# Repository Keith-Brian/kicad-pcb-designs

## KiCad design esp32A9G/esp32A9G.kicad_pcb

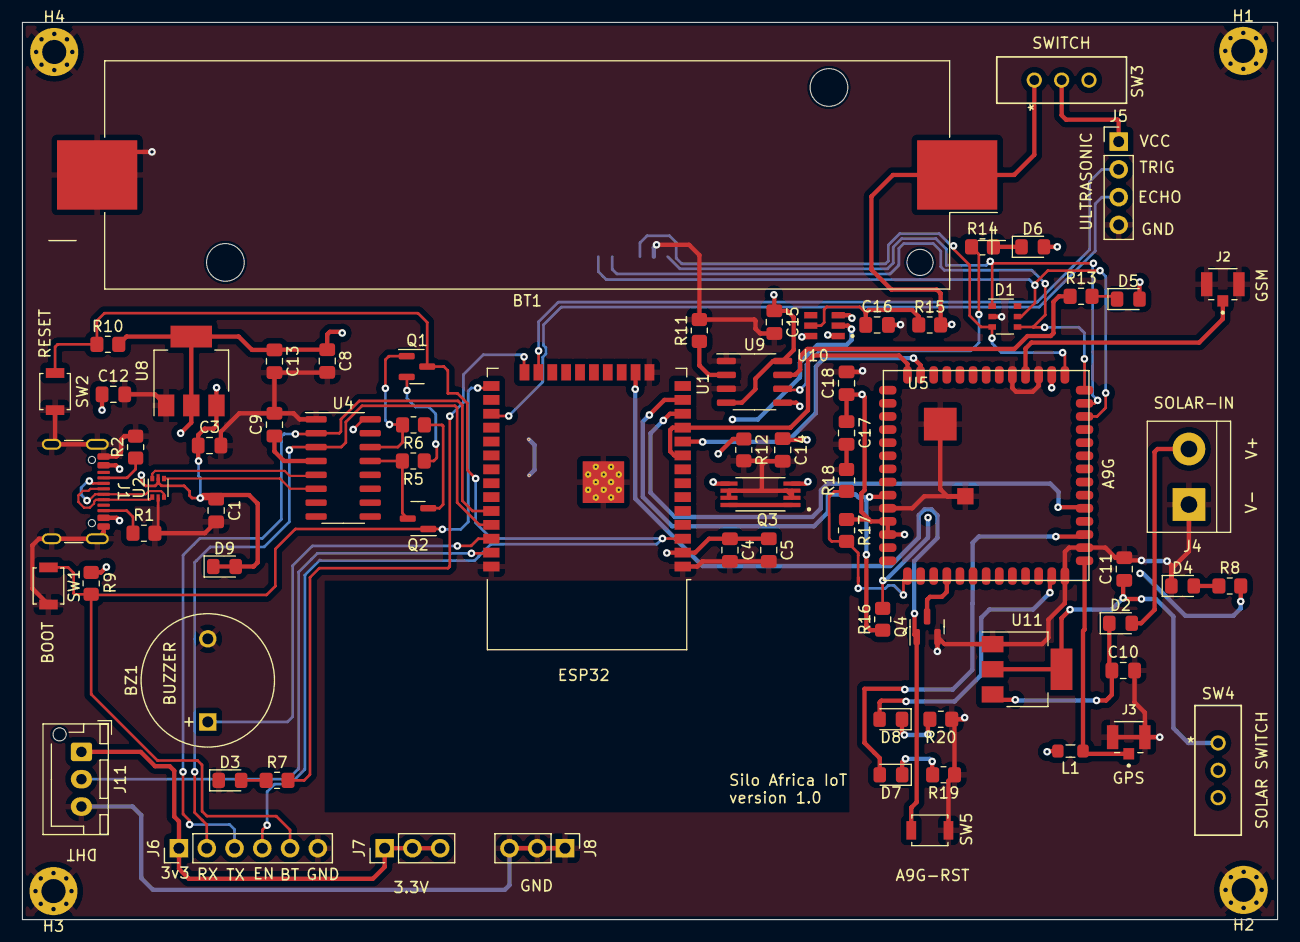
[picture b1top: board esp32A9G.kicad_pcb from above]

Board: 4 copper layers, 114.8 x 82.1 mm, 76 parts (1 on the bottom side), 57 nets.

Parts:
BT1: Battery; BatteryHolder_Keystone_1042_1x18650
BZ1: Buzzer; MagneticBuzzer_ProSignal_ABI-009-RC
C1, C4, C11, C12: 22uF; C_0805_2012Metric_Pad1.18x1.45mm_HandSolder
C3, C5, C8, C9: 0.1uF; C_0805_2012Metric_Pad1.18x1.45mm_HandSolder
C10, C13, C14, C15, C16, C17: 10uF; C_0805_2012Metric_Pad1.18x1.45mm_HandSolder
C18: 100uF; C_0805_2012Metric_Pad1.18x1.45mm_HandSolder
D1: SMF05C; TSOP-6_1.65x3.05mm_P0.95mm
D2: 1N4001; D_0805_2012Metric_Pad1.15x1.40mm_HandSolder
D3, D4, D5, D6, D7, D8: LED; LED_0805_2012Metric_Pad1.15x1.40mm_HandSolder
D9: D_Schottky; D_0805_2012Metric_Pad1.15x1.40mm_HandSolder
H1, H2, H3, H4: MountingHole_Pad; MountingHole_2.2mm_M2_Pad_Via
J1: USB_C_Receptacle_USB2.0; USB_C_Receptacle_GCT_USB4105-xx-A_16P_TopMnt_Horizontal
J2, J3: CONUFL001-SMD-T; LINX_CONUFL001-SMD-T
J4: Screw_Terminal_01x02; TerminalBlock_bornier-2_P5.08mm
J5: Conn_01x04_Pin; PinHeader_1x04_P2.54mm_Vertical
J6: Conn_01x06_Pin; PinHeader_1x06_P2.54mm_Vertical
J7, J8: Conn_01x03_Pin; PinHeader_1x03_P2.54mm_Vertical
J9: MICRO SIM; GCT_SIM7100-6-1-15-00-A_REVC
J11: Conn_01x03_Pin; JST_XH_B3B-XH-AM_1x03_P2.50mm_Vertical
L1: L; L_0805_2012Metric_Pad1.05x1.20mm_HandSolder
Q1: 2N3904; SOT-23
Q2: 2N3906; SOT-23
Q3: FS8205A; SOP65P640X120-8N
Q4: 2N7002; SOT-23
R1, R2: 5k1; R_0805_2012Metric_Pad1.20x1.40mm_HandSolder
R5, R9, R10, R16: 10k; R_0805_2012Metric_Pad1.20x1.40mm_HandSolder
R6: 10K; R_0805_2012Metric_Pad1.20x1.40mm_HandSolder
R7, R17, R18: 330E; R_0805_2012Metric_Pad1.20x1.40mm_HandSolder
R8, R12, R13, R14, R19, R20: 1k; R_0805_2012Metric_Pad1.20x1.40mm_HandSolder
R11: 1k6; R_0805_2012Metric_Pad1.20x1.40mm_HandSolder
R15: 100; R_0805_2012Metric_Pad1.20x1.40mm_HandSolder
SW1, SW2, SW5: SW_Push; SW_SPST_B3U-1000P
SW3: SW_SPST; slider
SW4: SW_SPDT; slider
U1: ESP32-WROOM-32D
U2: USBLC6-2P6; SOT-666
U4: CH340C; SOIC-16_3.9x9.9mm_P1.27mm
U5: A9G; A9
U8: LM1117MP-3.3; SOT-223-3_TabPin2
U9: TP4056; SO-8_3.9x4.9mm_P1.27mm
U10: DW01A; SOT95P280X145-6N
U11: AMS1117-5.0; SOT-223-3_TabPin2

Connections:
+3V3: C4.1, C5.1, C8.1, C13.1, J6.1, J7.1, J7.2, J7.3, J11.1, R8.2, R9.2, R10.2, U1.2 (VDD), U4.16 (VCC), U8.2 (VO)
/A9G_RST: Q4.1 (G), SW5.1, U1.16 (IO13)
/ADC_0: R17.2, R18.1, U5.15 (ADC0)
/BOOT: J6.5, Q2.1 (E), R9.1, SW1.1, U1.25 (IO0)
/BUZZER: BZ1.1 (-), U1.36 (IO22)
/D+: U2.6 (I/O1), U4.5 (UD+)
/D-: U2.4 (I/O2), U4.6 (UD-)
/DE+: J1.A6 (D+), J1.B6 (D+), U2.1 (I/O1)
/DE-: J1.A7 (D-), J1.B7 (D-), U2.3 (I/O2)
/DHT11: J11.2, U1.37 (IO23)
/DTR: Q2.3 (C), R5.2, U4.13 (~DTR)
/ECHO: J5.3, U1.27 (IO16)
/EN: J6.4, Q1.3 (C), R10.1, SW2.1, U1.3 (EN)
/GPRS_LED: D8.2 (A), U5.26 (IO27)
/GSM_LED: D7.2 (A), U5.30 (IO28)
/LED: R7.2, U1.24 (IO2)
/LOW_PWR: U1.12 (IO27), U5.32 (IO25)
/OC: Q3.4, U10.3 (OC)
/OD: Q3.5, U10.1 (OD)
/PWR_KEY: R16.1, U1.13 (IO14), U5.9 (PWRKEY)
/RTS: Q1.1 (E), R6.2, U4.14 (~RTS)
/RX: J6.2, U1.35 (TXD0/IO1), U4.3 (RXD)
/SIM_CLK: D1.4, J9.C3 (CLK), U5.41 (SIM_CLK)
/SIM_DATA: D1.5, J9.C7 (I/O), U5.39 (SIM_DIO)
/SIM_RST: D1.3, J9.C2 (RST), U5.42 (SIM_RST)
/SIM_VDD: D1.1, J9.C1 (VCC), U5.40 (VSIM)
/TRIG: J5.2, U1.23 (IO15)
/TX: J6.3, U1.34 (RXD0/IO3), U4.2 (TXD)
/UART_RX: U1.10 (IO25), U5.53 (UART1_RX)
/UART_TX: U1.9 (IO33), U1.11 (IO26), U5.54 (UART1_TX)
/V3: C9.1, U4.4 (V3)
/VIO: R16.2, U5.43 (V_IO)
BATT_IN: BT1.1 (+), C14.1, R15.2, SW3.1 (A), U9.5 (BAT)
GND: BT1.2 (-), BZ1.2 (+), C1.2, C3.2, C4.2, C5.2, C8.2, C9.2, C10.2, C11.2, C12.2, C13.2, C14.2, C15.2, C16.2, C17.2, C18.2, D1.2, D3.1 (K), D4.1 (K), H1.1, H2.1, H3.1, H4.1, J1.A1 (GND), J1.A12 (GND), J1.B1 (GND), J1.B12 (GND), J1.S1 (SHIELD), J2.2, J2.3, J3.2, J3.3, J4.1, J5.4, J6.6, J8.1, J8.2, J8.3, J9.C5 (GND), J11.3, Q3.2, Q3.3, Q3.6, Q3.7, Q4.2 (S), R1.2, R2.2, R11.2, R12.2, R18.2, R19.1, R20.1, SW1.2, SW2.2, SW5.2, U1.1 (GND), U1.15 (GND), U1.38 (GND), U1.39 (GND), U2.2 (GND), U4.1 (GND), U5.10 (GND), U5.27 (GND_1), U5.29 (GND_2), U5.44 (GND_3), U5.46 (GND_4), U5.55 (GND_5), U5.56 (GND_6), U8.1 (GND), U9.1 (TEMP), U9.3 (GND), U10.6 (GND), U11.1 (GND)
GPRS_RF: J2.1, U5.45 (GPRS_RF)
GPS_RF: J3.1, L1.1, U5.28 (GPS_RF)
unnamed: D2.2 (A), J4.2
unnamed: C10.1, D2.1 (K), U11.3 (VI)
unnamed: D3.2 (A), R7.1
unnamed: D4.2 (A), R8.1
unnamed: D5.1 (K), R13.2
unnamed: D6.1 (K), R14.2
unnamed: D7.1 (K), R19.2
unnamed: D8.1 (K), R20.2
unnamed: J1.A5 (CC1), R2.1
unnamed: J1.B5 (CC2), R1.1
unnamed: Q1.2 (B), R5.1
unnamed: Q2.2 (B), R6.1
unnamed: Q4.3 (D), U5.18 (RESET)
unnamed: R11.1, U9.2 (PROG)
unnamed: R13.1, U9.7 (~CHRG)
unnamed: R14.1, U9.6 (~STDBY)
unnamed: R12.1, U10.2 (CS)
unnamed: C16.1, R15.1, U10.5 (VCC)
SOLAR_IN: C11.1, SW4.1 (A), U11.2 (VO)
VBAT: C1.1, C3.1, C12.1, C17.1, C18.1, D9.1 (K), D9.2 (A), J1.A4 (VBUS), J1.A9 (VBUS), J1.B4 (VBUS), J1.B9 (VBUS), J5.1, L1.2, R17.1, SW3.2 (B), SW4.3 (C), U2.5 (VBUS), U5.11 (VBAT), U5.12 (VBATT), U8.3 (VI)
VCC: C15.1, D5.2 (A), D6.2 (A), SW4.2 (B), U9.4 (VCC), U9.8 (CE)

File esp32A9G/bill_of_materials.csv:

"Id";"Designator";"Footprint";"Quantity";"Designation";"Supplier and ref";
1;"C12,C11,C4,C1";"C_0805_2012Metric_Pad1.18x1.45mm_HandSolder";4;"22uF";;;
2;"D4,D3,D8,D7,D5,D6";"LED_0805_2012Metric_Pad1.15x1.40mm_HandSolder";6;"LED";;;
3;"C18";"C_0805_2012Metric_Pad1.18x1.45mm_HandSolder";1;"100uF";;;
4;"BT1";"BatteryHolder_Keystone_1042_1x18650";1;"Battery";;;
5;"C14,C17,C15,C16,C13,C10";"C_0805_2012Metric_Pad1.18x1.45mm_HandSolder";6;"10uF";;;
6;"R7,R18,R17";"R_0805_2012Metric_Pad1.20x1.40mm_HandSolder";3;"330E";;;
7;"D2";"D_0805_2012Metric_Pad1.15x1.40mm_HandSolder";1;"1N4001";;;
8;"SW3";"slider";1;"SW_SPST";;;
9;"SW5,SW2,SW1";"SW_SPST_B3U-1000P";3;"SW_Push";;;
10;"U4";"SOIC-16_3.9x9.9mm_P1.27mm";1;"CH340C";;;
11;"R12,R14,R20,R13,R8,R19";"R_0805_2012Metric_Pad1.20x1.40mm_HandSolder";6;"1k";;;
12;"H1,H2,H3,H4";"MountingHole_2.2mm_M2_Pad_Via";4;"MountingHole_Pad";;;
13;"L1";"L_0805_2012Metric_Pad1.05x1.20mm_HandSolder";1;"L";;;
14;"R11";"R_0805_2012Metric_Pad1.20x1.40mm_HandSolder";1;"1k6";;;
15;"J11";"JST_XH_B3B-XH-AM_1x03_P2.50mm_Vertical";1;"Conn_01x03_Pin";;;
16;"Q2";"SOT-23";1;"2N3906";;;
17;"C9,C5,C8,C3";"C_0805_2012Metric_Pad1.18x1.45mm_HandSolder";4;"0.1uF";;;
18;"R6";"R_0805_2012Metric_Pad1.20x1.40mm_HandSolder";1;"10K";;;
19;"J5";"PinHeader_1x04_P2.54mm_Vertical";1;"Conn_01x04_Pin";;;
20;"U11";"SOT-223-3_TabPin2";1;"AMS1117-5.0";;;
21;"R15";"R_0805_2012Metric_Pad1.20x1.40mm_HandSolder";1;"100";;;
22;"R10,R5,R16,R9";"R_0805_2012Metric_Pad1.20x1.40mm_HandSolder";4;"10k";;;
23;"J1";"USB_C_Receptacle_GCT_USB4105-xx-A_16P_TopMnt_Horizontal";1;"USB_C_Receptacle_USB2.0";;;
24;"Q3";"SOP65P640X120-8N";1;"FS8205A";;;
25;"BZ1";"MagneticBuzzer_ProSignal_ABI-009-RC";1;"Buzzer";;;
26;"Q4";"SOT-23";1;"2N7002";;;
27;"J7,J8";"PinHeader_1x03_P2.54mm_Vertical";2;"Conn_01x03_Pin";;;
28;"D9";"D_0805_2012Metric_Pad1.15x1.40mm_HandSolder";1;"D_Schottky";;;
29;"Q1";"SOT-23";1;"2N3904";;;
30;"J3,J2";"LINX_CONUFL001-SMD-T";2;"CONUFL001-SMD-T";;;
31;"U5";"A9";1;"A9G";;;
32;"J4";"TerminalBlock_bornier-2_P5.08mm";1;"Screw_Terminal_01x02";;;
33;"D1";"TSOP-6_1.65x3.05mm_P0.95mm";1;"SMF05C";;;
34;"SW4";"slider";1;"SW_SPDT";;;
35;"U1";"ESP32-WROOM-32D";1;"ESP32-WROOM-32D";;;
36;"U8";"SOT-223-3_TabPin2";1;"LM1117MP-3.3";;;
37;"R1,R2";"R_0805_2012Metric_Pad1.20x1.40mm_HandSolder";2;"5k1";;;
38;"U2";"SOT-666";1;"USBLC6-2P6";;;
39;"J6";"PinHeader_1x06_P2.54mm_Vertical";1;"Conn_01x06_Pin";;;
40;"U10";"SOT95P280X145-6N";1;"DW01A";;;
41;"U9";"SO-8_3.9x4.9mm_P1.27mm";1;"TP4056";;;
42;"J9";"GCT_SIM7100-6-1-15-00-A_REVC";1;"MICRO SIM";;;

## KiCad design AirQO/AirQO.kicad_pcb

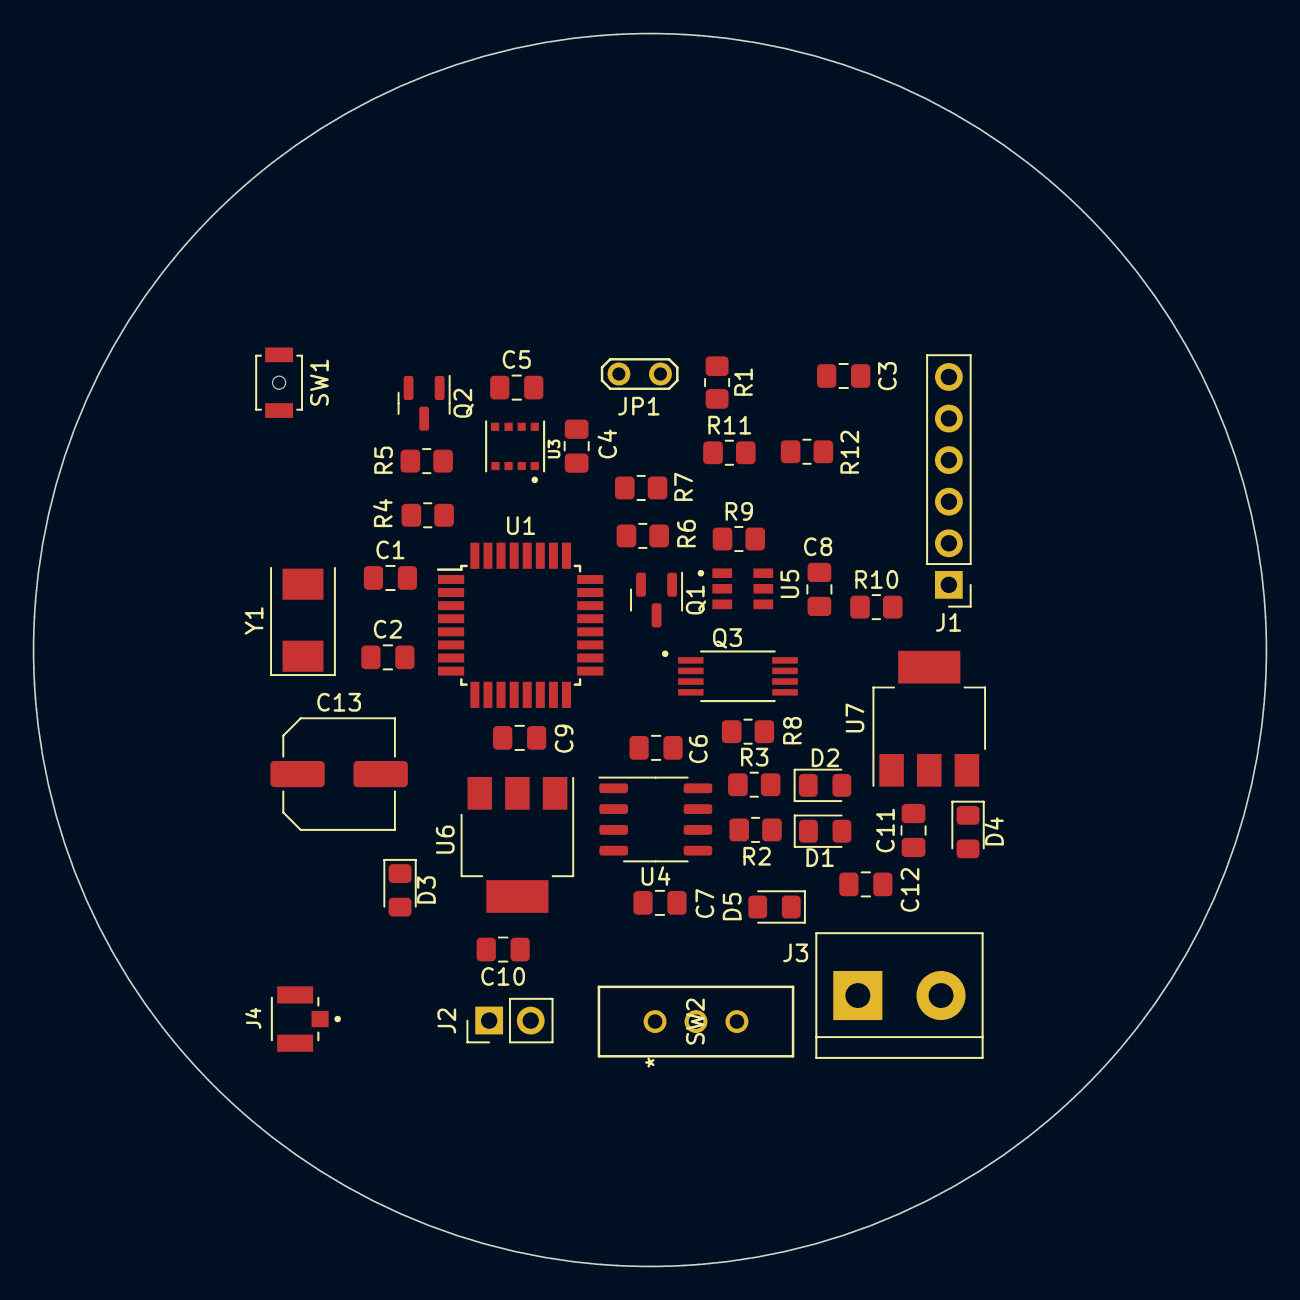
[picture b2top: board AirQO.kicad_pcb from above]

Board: 2 copper layers, 75.3 x 75.3 mm, 48 parts (1 on the bottom side), 35 nets, no tracks yet.

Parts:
C1, C2: 22pF; C_0805_2012Metric_Pad1.18x1.45mm_HandSolder
C3: 100nF; C_0805_2012Metric_Pad1.18x1.45mm_HandSolder
C4, C5: 0.1uF; C_0805_2012Metric_Pad1.18x1.45mm_HandSolder
C6, C7, C8, C10, C11: 10uF; C_0805_2012Metric_Pad1.18x1.45mm_HandSolder
C9, C12: 22uF; C_0805_2012Metric_Pad1.18x1.45mm_HandSolder
C13: 22pF; C_Elec_6.3x7.7
D1, D2: LED; LED_0805_2012Metric_Pad1.15x1.40mm_HandSolder
D3, D4, D5: 1N4001; D_0805_2012Metric_Pad1.15x1.40mm_HandSolder
J1: Conn_01x06_Pin; PinHeader_1x06_P2.54mm_Vertical
J2: Conn_01x02_Pin; PinHeader_1x02_P2.54mm_Vertical
J3: Screw_Terminal_01x02; TerminalBlock_bornier-2_P5.08mm
J4: CONUFL001-SMD-T; LINX_CONUFL001-SMD-T
JP1: Jumper_2_Open; TestPoint_2Pads_Pitch2.54mm_Drill0.8mm
Q1, Q2: 2N7002; SOT-23
Q3: FS8205A; SOP65P640X120-8N
R1, R4, R5, R6, R7: 10k; R_0805_2012Metric_Pad1.20x1.40mm_HandSolder
R2, R3, R9, R11, R12: 1k; R_0805_2012Metric_Pad1.20x1.40mm_HandSolder
R8: 1k6; R_0805_2012Metric_Pad1.20x1.40mm_HandSolder
R10: 100; R_0805_2012Metric_Pad1.20x1.40mm_HandSolder
SW1: SW_Push; SW_SPST_B3U-1000P-B
SW2: SW_SPDT; slider
U1: ATmega328P-A; TQFP-32_7x7mm_P0.8mm
U2: RFM95W-868S2; XCVR_RFM95W-868S2
U3: BME680; PSON80P300X300X100-8N
U4: TP4056; SO-8_3.9x4.9mm_P1.27mm
U5: DW01A; SOT95P280X145-6N
U6: LM1117MP-3.3; SOT-223-3_TabPin2
U7: AMS1117-5.0; SOT-223-3_TabPin2
Y1: Crystal; Crystal_SMD_0603-2Pin_6.0x3.5mm

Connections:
+3V3: C4.2, C5.1, C10.1, Q1.1 (G), Q2.1 (G), R6.2, R7.1, U2.13 (3_3V), U3.2 (CSB), U3.6 (VDDIO), U3.8 (VDD), U6.2 (VO)
/DI02: U1.2 (PD4), U2.16 (DIO2)
/MISO/12: U1.10 (PD6), U2.2 (MISO)
/MOSI/11: U1.9 (PD5), U2.3 (MOSI)
/NSS/4: U1.32 (PD2), U2.5 (NSS)
/OC: Q3.4, U5.3 (OC)
/OD: Q3.5, U5.1 (OD)
/RST: C3.2, R1.1, SW1.1, U1.29 (~RESET/PC6)
/RST/5: U1.1 (PD3), U2.6 (RESET)
/RX: J1.4, U1.30 (PD0)
/SCK/13: U1.11 (PD7), U2.4 (SCK)
/SCL: Q1.2 (S), R4.1, U1.28 (PC5)
/SCL_L: Q1.3 (D), R6.1, U3.4 (SCK)
/SDA: Q2.2 (S), R5.1, U1.27 (PC4)
/SDA_L: Q2.3 (D), R7.2, U3.3 (SDI)
/TX: J1.5, U1.31 (PD1)
/VBAT_ADC: R11.2, R12.1, U1.23 (PC0)
ANTENNA: J4.1, U2.9 (ANT)
BATT_IN: C7.1, J2.2, R10.2, SW2.1 (A), U4.5 (BAT)
GND: C1.2, C2.2, C4.1, C5.2, C6.2, C7.2, C8.2, C9.2, C10.2, C11.2, C12.2, C13.1, J1.1, J2.1, J3.1, J4.2, J4.3, Q3.2, Q3.3, Q3.6, Q3.7, R8.2, R9.2, R12.2, SW1.2, U1.3 (GND), U1.5 (GND), U1.21 (GND), U2.1 (GND), U2.8 (GND@1), U2.10 (GND@2), U3.1 (GND), U3.5 (SDO), U3.7 (GND), U4.1 (TEMP), U4.3 (GND), U5.6 (GND), U6.1 (GND), U7.1 (GND)
unnamed: D1.1 (K), R2.2
unnamed: D2.1 (K), R3.2
unnamed: D4.2 (A), J3.2
unnamed: C11.1, D4.1 (K), U7.3 (VI)
unnamed: J1.3, JP1.1 (A)
unnamed: C3.1, J1.6
unnamed: C1.1, U1.7 (XTAL1/PB6), Y1.2
unnamed: C2.1, U1.8 (XTAL2/PB7), Y1.1
unnamed: R8.1, U4.2 (PROG)
unnamed: R3.1, U4.7 (~CHRG)
unnamed: R2.1, U4.6 (~STDBY)
unnamed: R9.1, U5.2 (CS)
unnamed: C8.1, R10.1, U5.5 (VCC)
SOLAR: C6.1, C12.1, D1.2 (A), D2.2 (A), D5.1 (K), U4.4 (VCC), U4.8 (CE), U7.2 (VO)
VBAT: C9.1, C13.2, D3.1 (K), D3.2 (A), D5.2 (A), JP1.2 (B), R1.2, R4.2, R5.2, R11.1, SW2.2 (B), U1.4 (VCC), U1.6 (VCC), U1.18 (AVCC), U6.3 (VI)

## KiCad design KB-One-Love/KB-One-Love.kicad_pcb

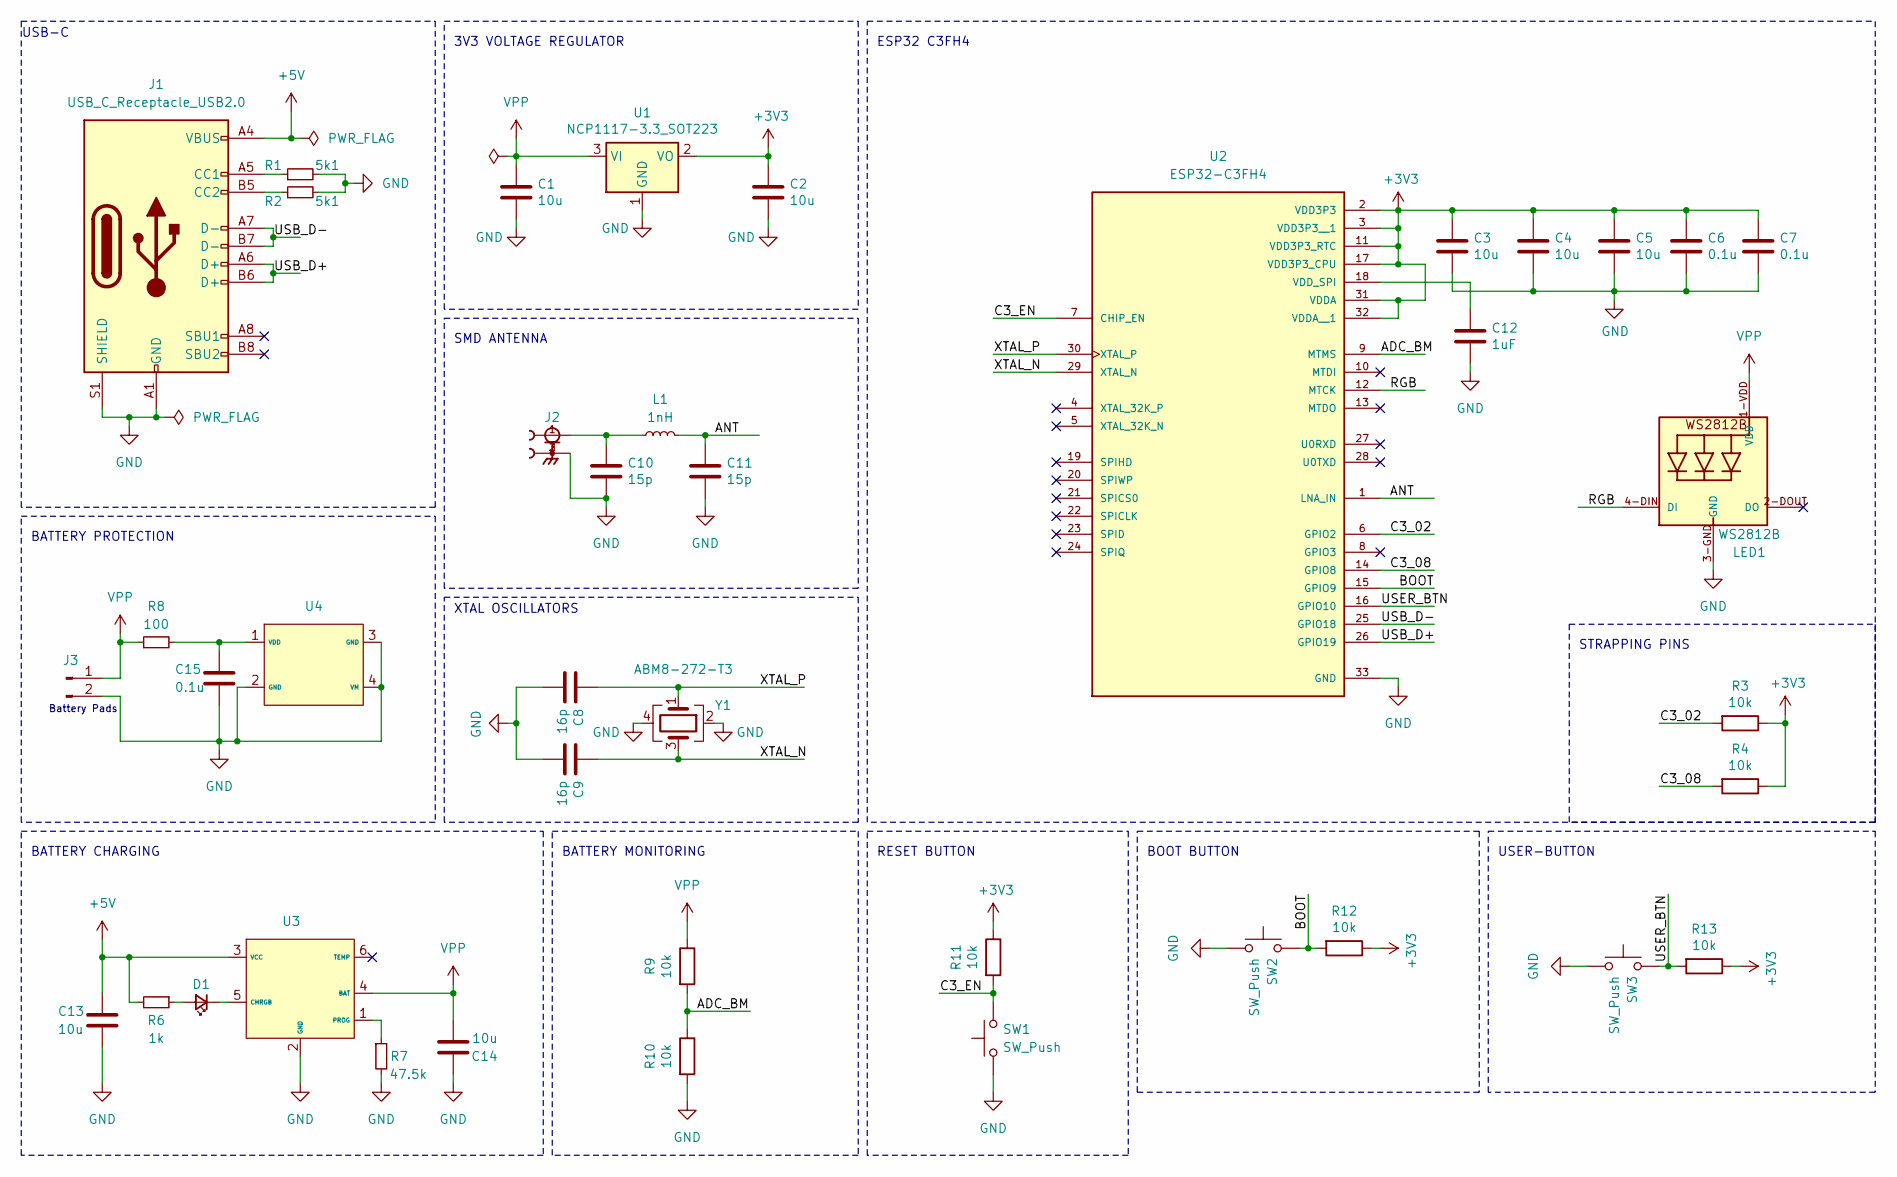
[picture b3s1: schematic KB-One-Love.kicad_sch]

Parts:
C1, C2, C3, C4, C5, C13, C14: 10u; C_0805_2012Metric_Pad1.18x1.45mm_HandSolder
C6, C7, C15: 0.1u; C_0805_2012Metric_Pad1.18x1.45mm_HandSolder
C8, C9: 16p; C_0805_2012Metric_Pad1.18x1.45mm_HandSolder
C10, C11: 15p; C_0805_2012Metric_Pad1.18x1.45mm_HandSolder
C12: 1uF; C_0805_2012Metric_Pad1.18x1.45mm_HandSolder
D1: LED_Small; LED_0805_2012Metric_Pad1.15x1.40mm_HandSolder
J1: USB_C_Receptacle_USB2.0; USB_C_Receptacle_GCT_USB4105-xx-A_16P_TopMnt_Horizontal
J2: CONUFL001-SMD-T; XDCR_AMCA31-2R450G-S1F-T3; PARTREV B
J3: Conn_01x02_Pin; JST_PH_B2B-PH-K_1x02_P2.00mm_Vertical
L1: 1nH; L_0402_1005Metric
LED1: WS2812B
R1, R2: 5k1; R_0805_2012Metric_Pad1.20x1.40mm_HandSolder
R3, R4, R9, R10, R11, R12, R13: 10k; R_0805_2012Metric_Pad1.20x1.40mm_HandSolder
R6: 1k; R_0805_2012Metric_Pad1.20x1.40mm_HandSolder
R7: 47.5k; R_0805_2012Metric_Pad1.20x1.40mm_HandSolder
R8: 100; R_0805_2012Metric_Pad1.20x1.40mm_HandSolder
SW1, SW2: SW_Push; SW_SPST_B3U-1000P
SW3: SW_Push; SW_SPST_PTS645
U1: NCP1117-3.3_SOT223; SOT-223-3_TabPin2
U2: ESP32-C3FH4; QFN50P500X500X90-33N; PARTREV V1.0
U3: ST_UQFN-6L_1.5x1.7mm_P0.5mm
U4: Mini-Circuits_FG873-4_3x3mm
Y1: ABM8-272-T3; Crystal_SMD_3225-4Pin_3.2x2.5mm

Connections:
+3V3: C2.1, C3.1, C4.1, C5.1, C6.1, C7.1, R3.1, R4.1, R11.1, R12.1, R13.1, U1.2 (VO), U2.2 (VDD3P3), U2.3 (VDD3P3__1), U2.11 (VDD3P3_RTC), U2.17 (VDD3P3_CPU), U2.31 (VDDA), U2.32 (VDDA__1)
+5V: C13.1, J1.A4 (VBUS), J1.A9 (VBUS), J1.B4 (VBUS), J1.B9 (VBUS), R6.2, U3.3 (VCC)
/ADC_BM: R9.2, R10.1, U2.9 (MTMS)
/ANT: C11.1, L1.2, U2.1 (LNA_IN)
/BOOT: R12.2, SW2.2, U2.15 (GPIO9)
/C3_02: R3.2, U2.6 (GPIO2)
/C3_08: R4.2, U2.14 (GPIO8)
/C3_EN: R11.2, SW1.2, U2.7 (CHIP_EN)
/RGB: LED1.4-DIN (DI), U2.12 (MTCK)
/USB_D+: J1.A6 (D+), J1.B6 (D+), U2.26 (GPIO19)
/USB_D-: J1.A7 (D-), J1.B7 (D-), U2.25 (GPIO18)
/USER_BTN: R13.2, SW3.2, U2.16 (GPIO10)
/XTAL_N: C9.1, U2.29 (XTAL_N), Y1.3
/XTAL_P: C8.1, U2.30 (XTAL_P), Y1.1
GND: C1.2, C2.2, C3.2, C4.2, C5.2, C6.2, C7.2, C8.2, C9.2, C10.2, C11.2, C12.2, C13.2, C14.1, C15.2, J1.A1 (GND), J1.A12 (GND), J1.B1 (GND), J1.B12 (GND), J1.S1 (SHIELD), J2.2, J2.3, J3.2, LED1.3-GND (GND), R1.2, R2.2, R7.2, R10.2, SW1.1, SW2.1, SW3.1, U1.1 (GND), U2.33 (GND), U3.2 (GND), U4.2 (GND), U4.3 (GND), U4.4 (VM), Y1.2, Y1.4
unnamed: C10.1, J2.1, L1.1
unnamed: D1.2 (A), R6.1
unnamed: D1.1 (K), U3.5 (CHRGB)
unnamed: J1.A5 (CC1), R1.1
unnamed: J1.B5 (CC2), R2.1
unnamed: C12.1, U2.18 (VDD_SPI)
unnamed: R7.1, U3.1 (PROG)
unnamed: C15.1, R8.2, U4.1 (VDD)
VPP: C1.1, C14.2, J3.1, LED1.1-VDD (VDD), R8.1, R9.1, U1.3 (VI), U3.4 (BAT)

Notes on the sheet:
BATTERY CHARGING
USB-C
Battery Pads
XTAL OSCILLATORS
SMD ANTENNA
RESET BUTTON
USER-BUTTON
ESP32 C3FH4
BATTERY MONITORING
3V3 VOLTAGE REGULATOR
STRAPPING PINS
BATTERY PROTECTION
BOOT BUTTON

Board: 2 copper layers, 41 parts (11 on the bottom side), 24 nets, no tracks yet.

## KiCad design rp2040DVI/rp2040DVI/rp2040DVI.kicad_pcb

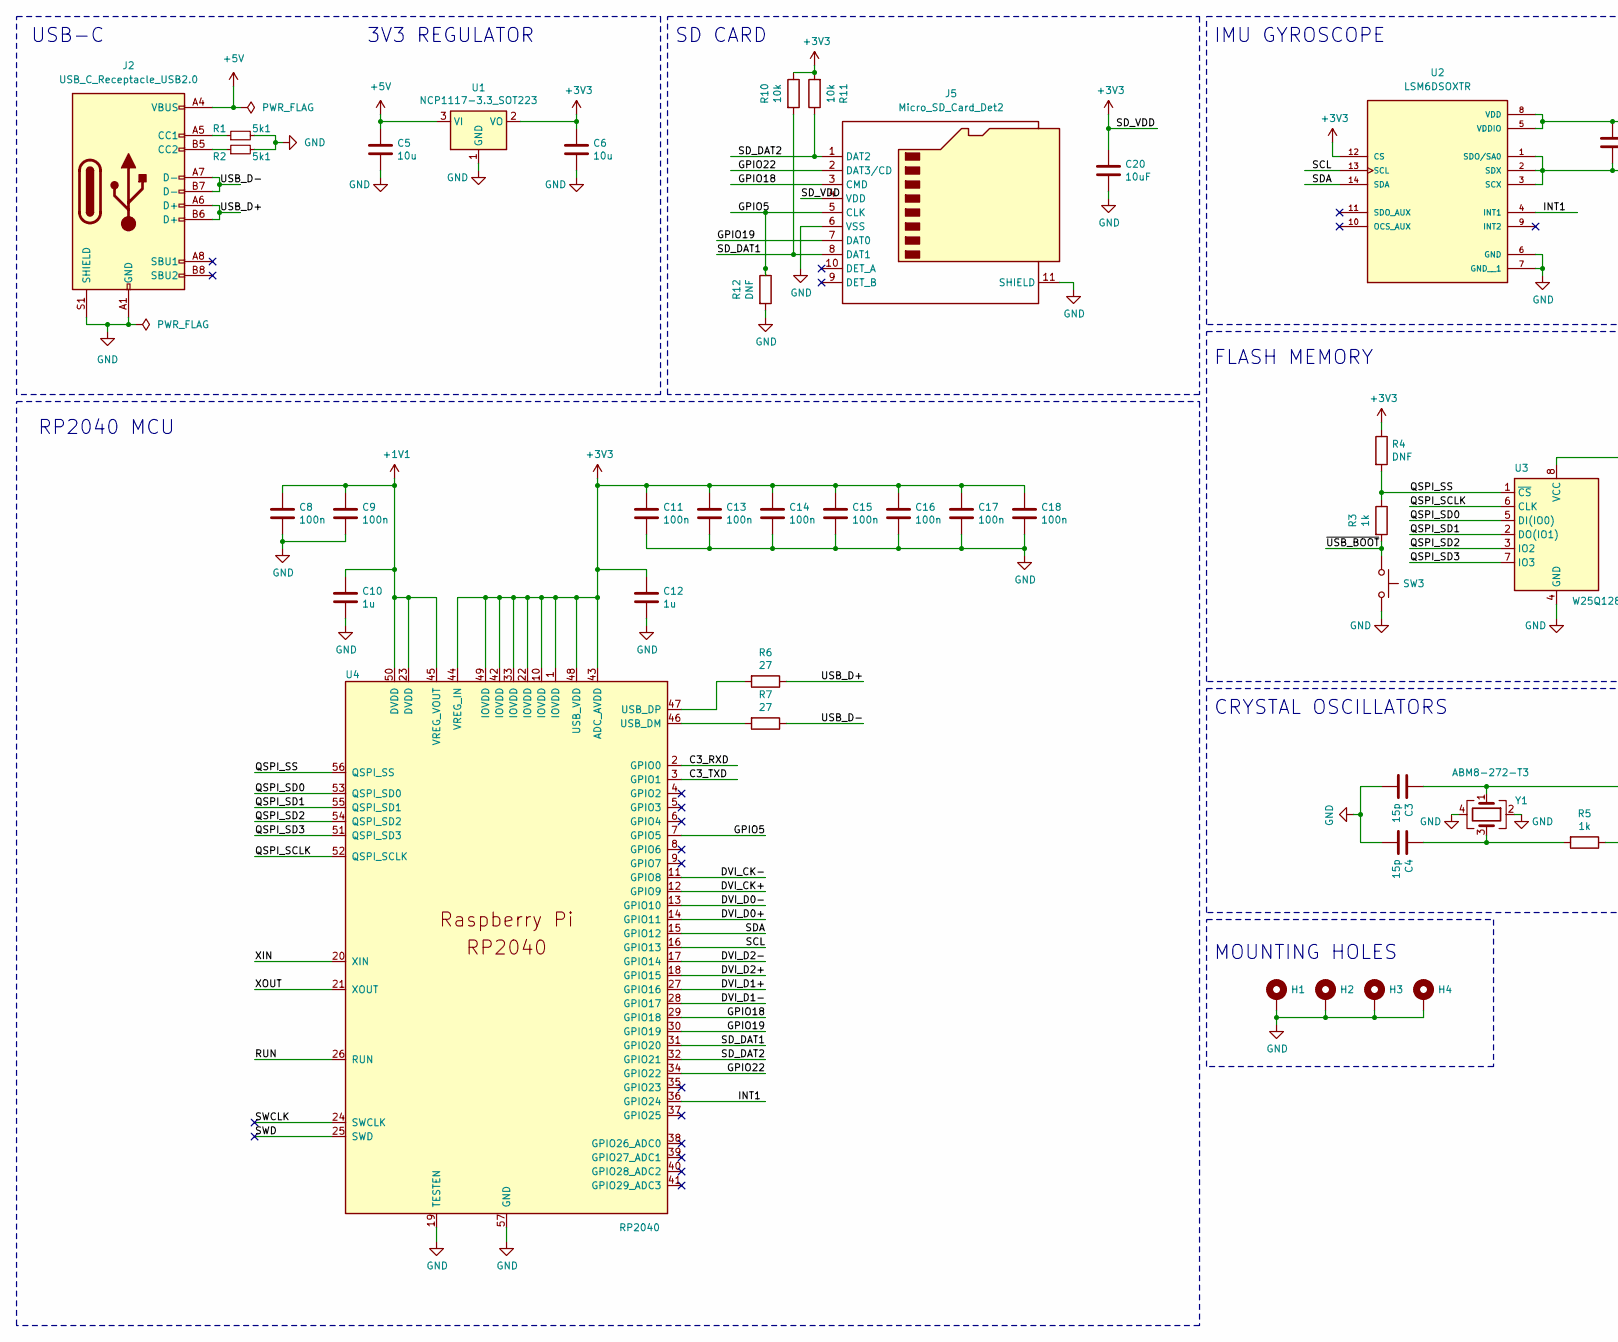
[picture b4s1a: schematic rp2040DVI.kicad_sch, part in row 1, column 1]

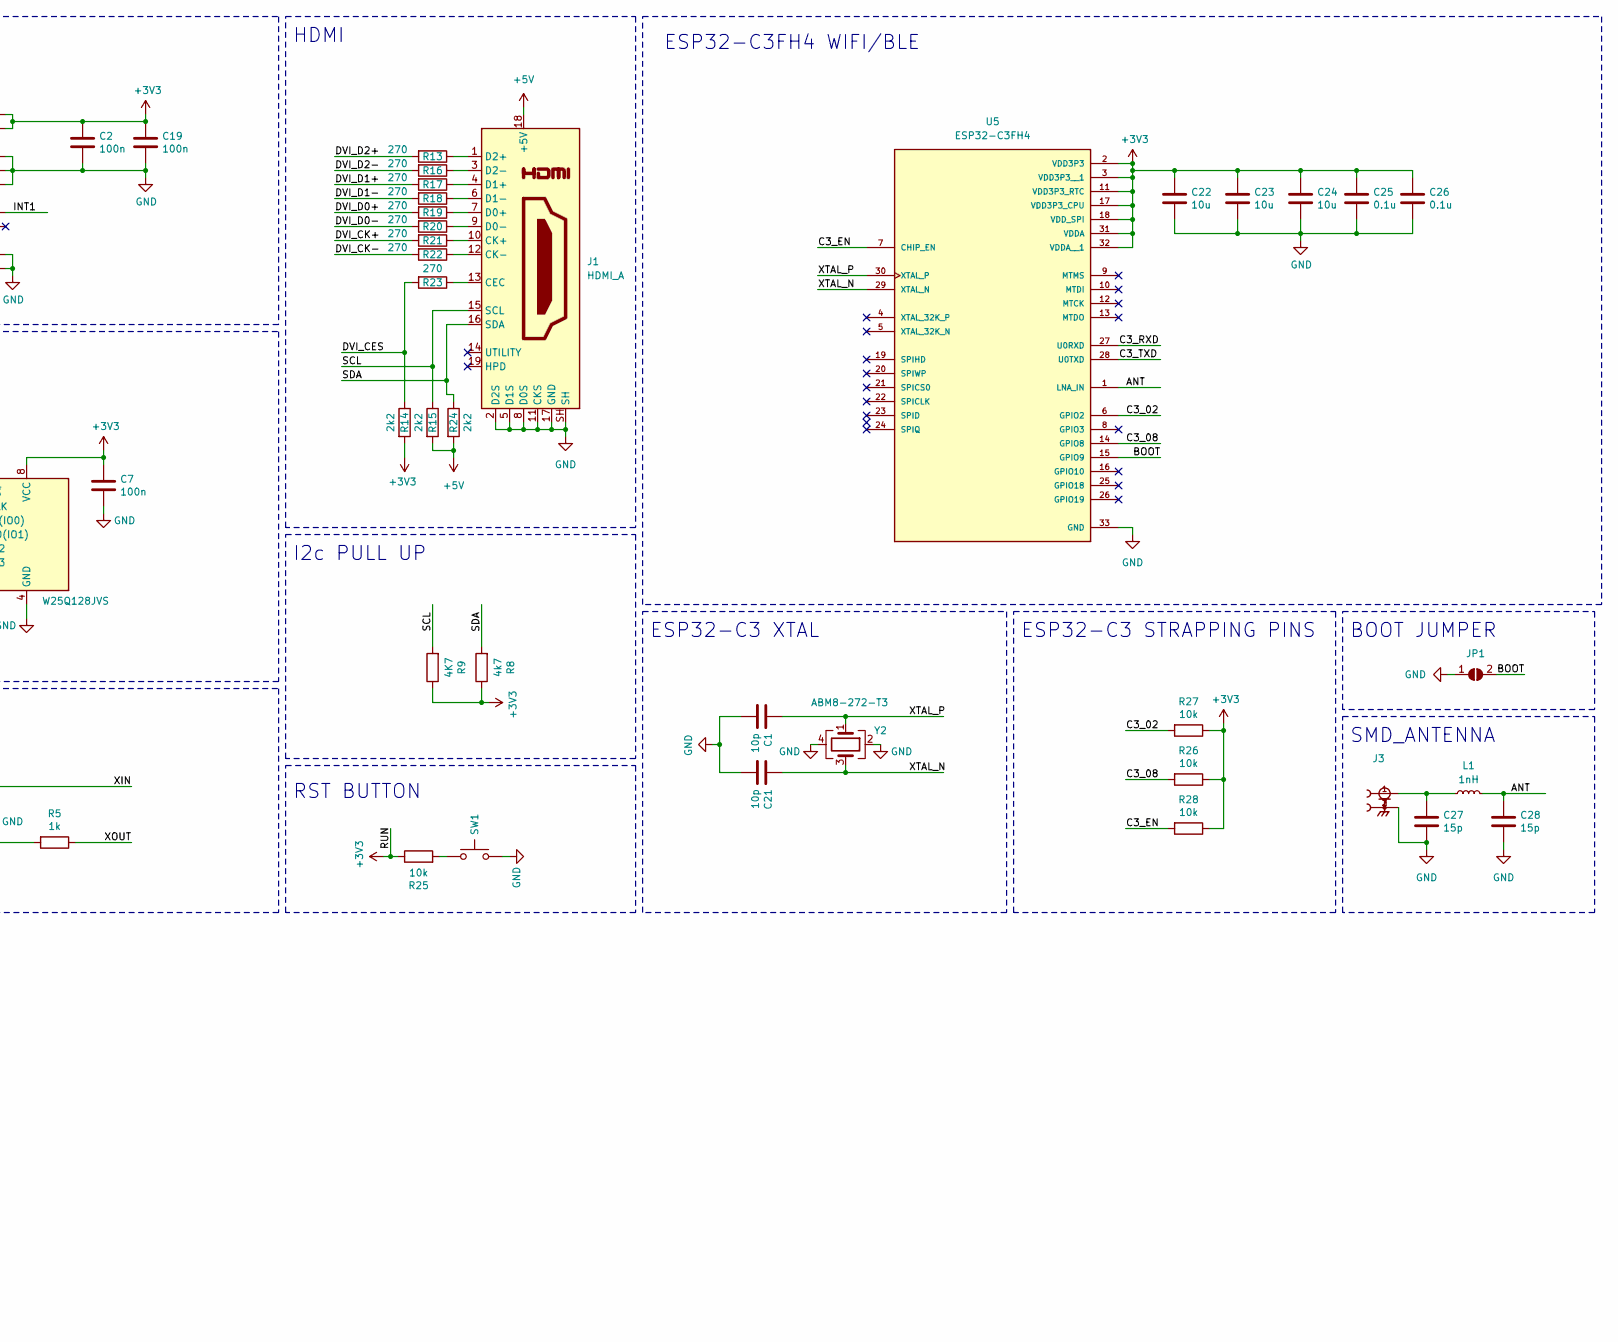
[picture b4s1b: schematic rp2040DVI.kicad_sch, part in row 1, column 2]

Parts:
C1, C21: 10p; C_0402_1005Metric
C2, C7, C8, C9, C11, C13, C14, C15, C16, C17, C18, C19: 100n; C_0402_1005Metric
C3, C4, C27, C28: 15p; C_0402_1005Metric
C5, C6: 10u; C_0805_2012Metric
C10, C12: 1u; C_0402_1005Metric
C20: 10uF; C_0402_1005Metric
C22, C23, C24: 10u; C_0402_1005Metric
C25, C26: 0.1u; C_0402_1005Metric
H1, H2, H3, H4: MountingHole_Pad; MountingHole_2.2mm_M2_Pad_Via
J1: HDMI_A; HDMI_A_Molex_208658-1001_Horizontal
J2: USB_C_Receptacle_USB2.0; USB_C_Receptacle_GCT_USB4105-xx-A_16P_TopMnt_Horizontal
J3: CONUFL001-SMD-T; XDCR_AMCA31-2R450G-S1F-T3; PARTREV B
J5: Micro_SD_Card_Det2; microSD_HC_Hirose_DM3D-SF
JP1: SolderJumper_2_Open; SolderJumper-2_P1.3mm_Open_TrianglePad1.0x1.5mm
L1: 1nH; L_0402_1005Metric
R1, R2: 5k1; R_0402_1005Metric
R3, R5: 1k; R_0402_1005Metric
R4, R12: DNF; R_0402_1005Metric
R6, R7: 27; R_0402_1005Metric
R8: 4k7; R_0402_1005Metric
R9: 4K7; R_0402_1005Metric
R10, R11, R25, R26, R27, R28: 10k; R_0402_1005Metric
R13, R16, R17, R18, R19, R20, R21, R22, R23: 270; R_0402_1005Metric
R14, R15, R24: 2k2; R_0402_1005Metric
SW1, SW3: SW_Push; SW_SPST_B3U-1000P
U1: NCP1117-3.3_SOT223; SOT-223-3_TabPin2
U2: LSM6DSOXTR; PQFN50P250X300X86-14N; PARTREV 3.0
U3: W25Q128JVS; SOIC-8_5.23x5.23mm_P1.27mm
U4: RP2040; QFN40P700X700X90-57N
U5: ESP32-C3FH4; QFN50P500X500X90-33N; PARTREV V1.0
Y1, Y2: ABM8-272-T3; Crystal_SMD_3225-4Pin_3.2x2.5mm

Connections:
+1V1: C8.1, C9.1, C10.1, U4.23 (DVDD), U4.45 (VREG_VOUT), U4.50 (DVDD)
+3V3: C2.1, C6.1, C7.1, C11.1, C12.1, C13.1, C14.1, C15.1, C16.1, C17.1, C18.1, C19.1, C20.1, C22.1, C23.1, C24.1, C25.1, C26.1, J5.4 (VDD), R4.1, R8.1, R9.1, R10.1, R11.2, R14.2, R25.1, R26.1, R27.1, R28.1, U1.2 (VO), U2.5 (VDDIO), U2.8 (VDD), U2.12 (CS), U3.8 (VCC), U4.1 (IOVDD), U4.10 (IOVDD), U4.22 (IOVDD), U4.26 (RUN), U4.33 (IOVDD), U4.42 (IOVDD), U4.43 (ADC_AVDD), U4.44 (VREG_IN), U4.48 (USB_VDD), U4.49 (IOVDD), U5.2 (VDD3P3), U5.3 (VDD3P3__1), U5.11 (VDD3P3_RTC), U5.17 (VDD3P3_CPU), U5.18 (VDD_SPI), U5.31 (VDDA), U5.32 (VDDA__1)
+5V: C5.1, J1.18 (+5V), J2.A4 (VBUS), J2.A9 (VBUS), J2.B4 (VBUS), J2.B9 (VBUS), R15.2, R24.2, U1.3 (VI)
/ANT: C28.1, L1.2, U5.1 (LNA_IN)
/BOOT: JP1.2 (B), U5.15 (GPIO9); also elsewhere on the board
/C3_02: R27.2, U5.6 (GPIO2)
/C3_08: R26.2, U5.14 (GPIO8)
/C3_EN: R28.2, U5.7 (CHIP_EN)
/C3_RXD: U4.2 (GPIO0), U5.27 (U0RXD)
/C3_TXD: U4.3 (GPIO1), U5.28 (U0TXD)
/DVI_CES: R14.1, R23.2
/DVI_CK+: R21.2, U4.12 (GPIO9)
/DVI_CK-: R22.2, U4.11 (GPIO8)
/DVI_D0+: R19.2, U4.14 (GPIO11)
/DVI_D0-: R20.2, U4.13 (GPIO10)
/DVI_D1+: R17.2, U4.27 (GPIO16)
/DVI_D1-: R18.2, U4.28 (GPIO17)
/DVI_D2+: R13.2, U4.18 (GPIO15)
/DVI_D2-: R16.2, U4.17 (GPIO14)
/GPIO5: J5.5 (CLK), R12.1, U4.7 (GPIO5)
/GPIO18: J5.3 (CMD), U4.29 (GPIO18)
/GPIO19: J5.7 (DAT0), U4.30 (GPIO19)
/GPIO22: J5.2 (DAT3/CD), U4.34 (GPIO22)
/INT1: U2.4 (INT1), U4.36 (GPIO24)
/QSPI_SCLK: U3.6 (CLK), U4.52 (QSPI_SCLK)
/QSPI_SD0: U3.5 (DI(IO0)), U4.53 (QSPI_SD0)
/QSPI_SD1: U3.2 (DO(IO1)), U4.55 (QSPI_SD1)
/QSPI_SD2: U3.3 (IO2), U4.54 (QSPI_SD2)
/QSPI_SD3: U3.7 (IO3), U4.51 (QSPI_SD3)
/QSPI_SS: R3.1, R4.2, U3.1 (~CS), U4.56 (QSPI_SS)
/SCL: J1.15 (SCL), R9.2, R15.1, U2.13 (SCL), U4.16 (GPIO13)
/SDA: J1.16 (SDA), R8.2, R24.1, U2.14 (SDA), U4.15 (GPIO12)
/SD_DAT1: J5.8 (DAT1), R10.2, U4.31 (GPIO20)
/SD_DAT2: J5.1 (DAT2), R11.1, U4.32 (GPIO21)
/SWCLK: U4.24 (SWCLK)
/SWD: U4.25 (SWD)
/USB_D+: J2.A6 (D+), J2.B6 (D+), R6.1
/USB_D-: J2.A7 (D-), J2.B7 (D-), R7.1
/XIN: C3.1, U4.20 (XIN), Y1.1
/XOUT: R5.1, U4.21 (XOUT)
/XTAL_N: C21.1, U5.29 (XTAL_N), Y2.3
/XTAL_P: C1.1, U5.30 (XTAL_P), Y2.1
/~USB_BOOT: R3.2; also elsewhere on the board
GND: C1.2, C2.2, C3.2, C4.2, C5.2, C6.2, C7.2, C8.2, C9.2, C10.2, C11.2, C12.2, C13.2, C14.2, C15.2, C16.2, C17.2, C18.2, C19.2, C20.2, C21.2, C22.2, C23.2, C24.2, C25.2, C26.2, C27.2, C28.2, H1.1, H2.1, J1.2 (D2S), J1.5 (D1S), J1.8 (D0S), J1.11 (CKS), J1.17 (GND), J1.SH, J2.A1 (GND), J2.A12 (GND), J2.B1 (GND), J2.B12 (GND), J2.S1 (SHIELD), J3.2, J3.3, J5.6 (VSS), J5.11 (SHIELD), R1.2, R2.2, R12.2, U1.1 (GND), U2.1 (SDO/SA0), U2.2 (SDX), U2.3 (SCX), U2.6 (GND), U2.7 (GND__1), U3.4 (GND), U4.19 (TESTEN), U4.57 (GND), U5.33 (GND), Y1.2, Y1.4, Y2.2, Y2.4; also elsewhere on the board
unnamed: C4.1, R5.2, Y1.3
unnamed: C27.1, J3.1, L1.1
unnamed: J1.13 (CEC), R23.1
unnamed: J1.10 (CK+), R21.1
unnamed: J1.12 (CK-), R22.1
unnamed: J1.7 (D0+), R19.1
unnamed: J1.9 (D0-), R20.1
unnamed: J1.4 (D1+), R17.1
unnamed: J1.6 (D1-), R18.1
unnamed: J1.1 (D2+), R13.1
unnamed: J1.3 (D2-), R16.1
unnamed: J2.A5 (CC1), R1.1
unnamed: J2.B5 (CC2), R2.1
unnamed 57: R25.2; also elsewhere on the board
unnamed: R7.2, U4.46 (USB_DM)
unnamed: R6.2, U4.47 (USB_DP)

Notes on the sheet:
CRYSTAL OSCILLATORS
RST BUTTON
SMD_ANTENNA
ESP32-C3FH4 WIFI/BLE
MOUNTING HOLES
IMU GYROSCOPE
USB-C
ESP32-C3 XTAL
RP2040 MCU
HDMI
BOOT JUMPER
3V3 REGULATOR
FLASH MEMORY
I2c PULL UP
ESP32-C3 STRAPPING PINS
SD CARD

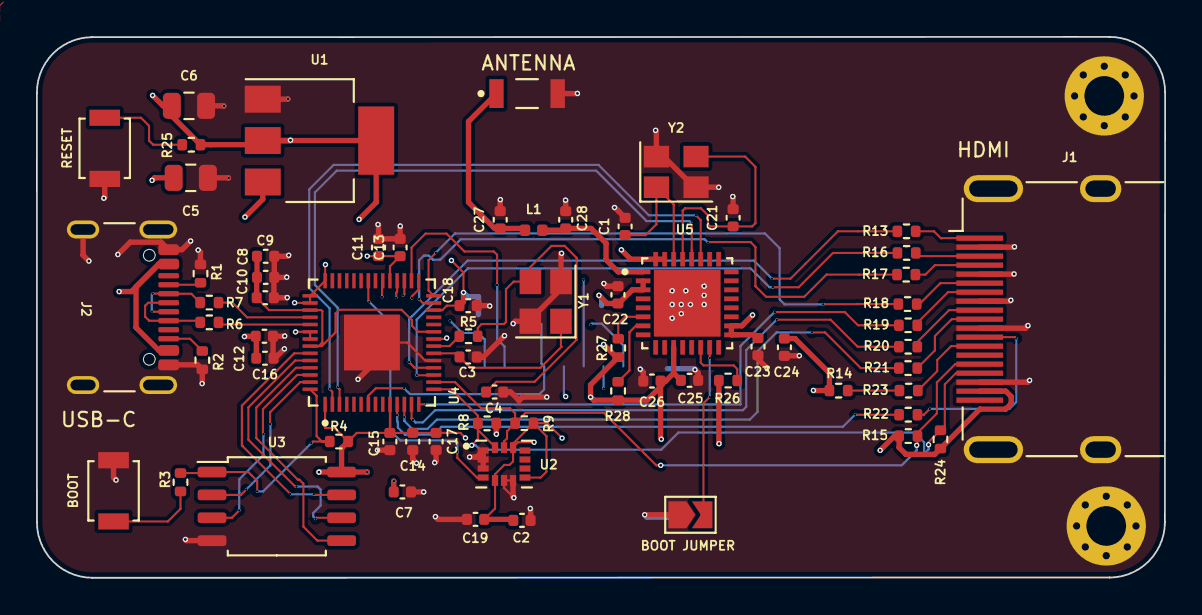
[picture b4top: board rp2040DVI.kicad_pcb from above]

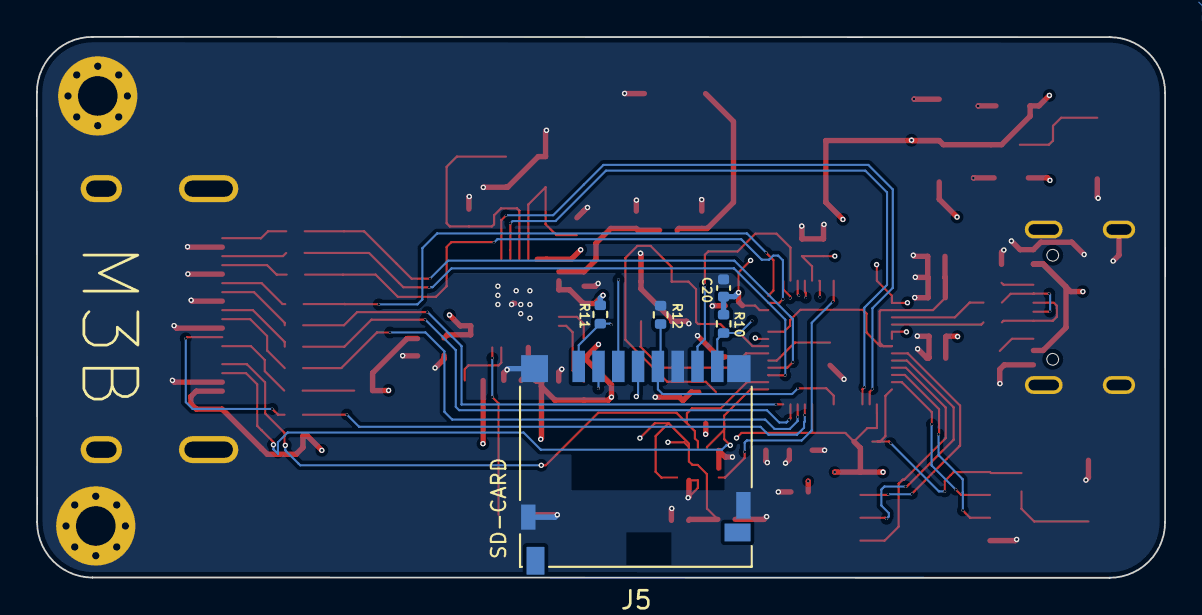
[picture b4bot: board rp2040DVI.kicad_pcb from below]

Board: 4 copper layers, 62.7 x 30.0 mm, 73 parts (5 on the bottom side), 58 nets.

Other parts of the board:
BOOT: SW_Push; SW_SPST_B3U-1000P
BOOT JUMPER: SolderJumper_2_Open; SolderJumper-2_P1.3mm_Open_TrianglePad1.0x1.5mm
RESET: SW_Push; SW_SPST_B3U-1000P

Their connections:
/BOOT: BOOT JUMPER.2 (B); also elsewhere on the board
/~USB_BOOT: BOOT.1; also elsewhere on the board
GND: BOOT.2, BOOT JUMPER.1 (A), RESET.2; also elsewhere on the board
unnamed 57: RESET.1; also elsewhere on the board

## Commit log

2024-04-02 added home automation pcb design
2024-04-02 added home automation image
2024-04-08 designed rp2040 DVI
2024-04-27 added other designs
